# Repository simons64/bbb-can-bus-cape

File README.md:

# bbb-can-bus-cape
beaglebone black cape:
- 4x CANbus (up to 1Mbit, 2x direct CAN, 2x MCP2515)
- 1x RS485 up to 10 Mbit

## __design untested yet !__

Credits for the design to [@voloviq/bbb-can-bus-cape](https://github.com/voloviq/bbb-can-bus-cape)  
Design was adjusted for:
- currently available components from jlcpcb
- compatible interface for home ESS (Victron Multiplus 2 ; Victron MPPT RS 450 ; Pylontech US5000C)

## board 3D view

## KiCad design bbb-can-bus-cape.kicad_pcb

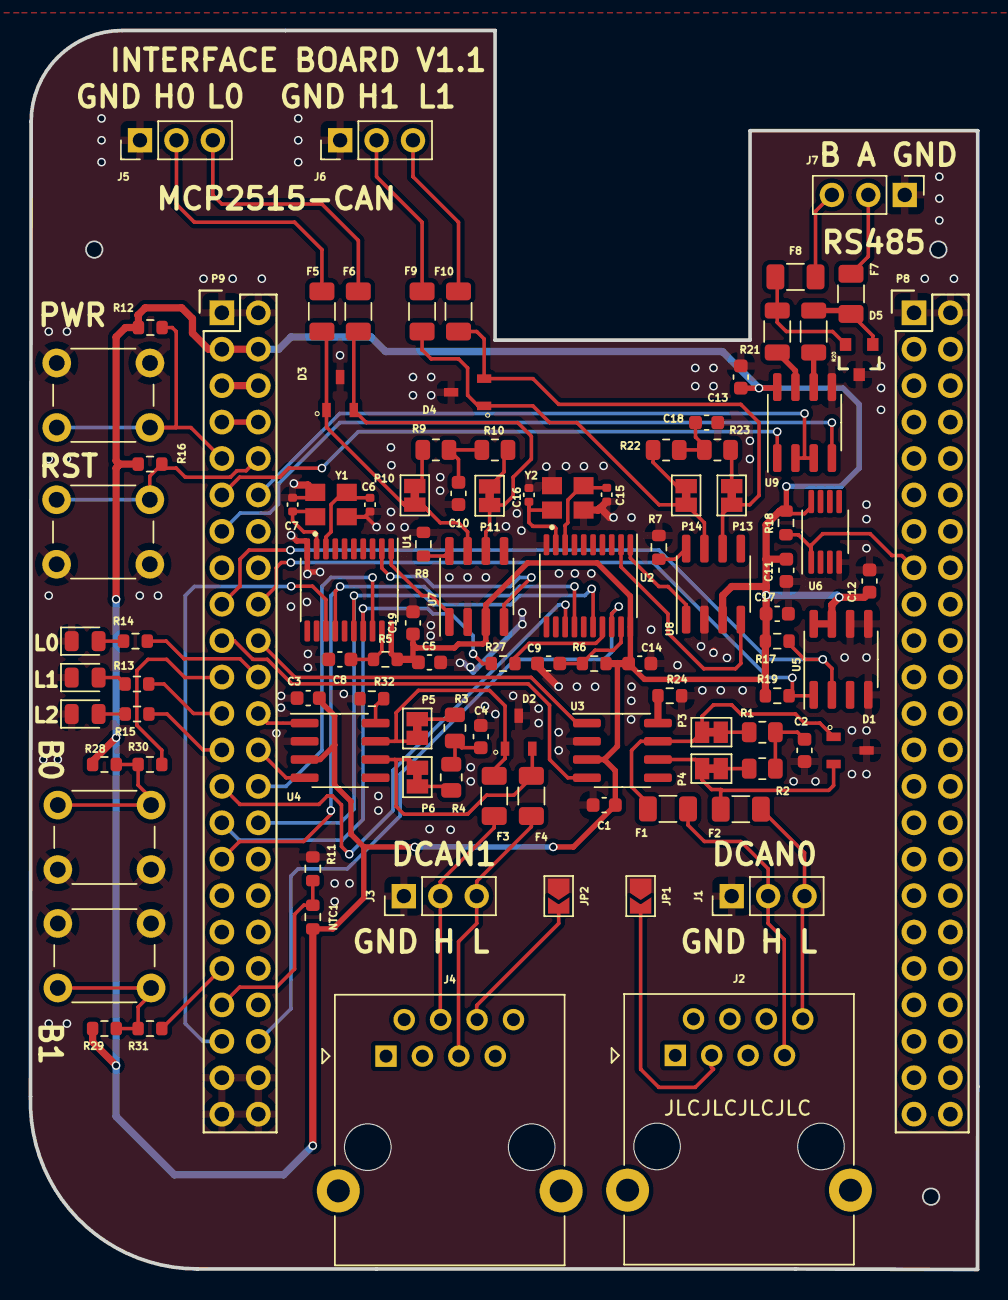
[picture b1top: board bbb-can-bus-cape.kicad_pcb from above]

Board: 2 copper layers, 66.0 x 86.4 mm, 102 parts (0 on the bottom side), 85 nets.

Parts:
C1, C2, C3, C4, C5, C8, C9, C10, C11, C12, C13, C14, C17, C18, C19: 100nF/50V; C_0603_1608Metric
C6, C7, C15, C16: 10pF/50V; C_0402_1005Metric
D1, D2, D3, D4: PESD2CAN,215; SOT95P230X110-3N
D5: PSM712; SOT23-3
D6, D7, D8: LED; D_0805_2012Metric
F1, F2, F3, F4, F5, F6, F7, F8, F9, F10: Polyfuse_Small; Fuse_1206_3216Metric
J1: Conn_DCAN0; PinHeader_1x03_P2.54mm_Vertical
J2: RJ45 BBB-DCAN0; RJ45_Ninigi_GE
J3: Conn_DCAN1; PinHeader_1x03_P2.54mm_Vertical
J4: RJ45 BBB-DCAN1; RJ45_Ninigi_GE
J5: Conn_MCP2515_CAN0; PinHeader_1x03_P2.54mm_Vertical
J6: Conn_MCP2515_CAN1; PinHeader_1x03_P2.54mm_Vertical
J7: Conn_RS485; PinHeader_1x03_P2.54mm_Vertical
JP1, JP2: J2_Open; SolderJumper-2_P1.3mm_Open_TrianglePad1.0x1.5mm
NTC1: NTCS0603E3103FMT; R_0603_1608Metric
P3, P4, P5, P6, P10, P11, P13, P14: TERM; SolderJumper-2_P1.3mm_Bridged_Pad1.0x1.5mm
P8, P9: BeagleBone_Black_Header; Socket_BeagleBone_Black
R1, R2, R3, R4, R9, R10, R22, R23: 60R; R_0805_2012Metric
R5, R6, R7, R8, R24, R32: 10k; R_0603_1608Metric
R11, R12, R16, R17, R18, R19, R28, R29: 4k7; R_0603_1608Metric
R13, R14, R15, R27, R30, R31: 100R; R_0603_1608Metric
R20, R21: 10R; R_1206_3216Metric
Sw1, Sw2, Sw3, Sw4: DTSM-31N; SW_PUSH_6mm
U1, U2: MCP2515-xST; TSSOP-20_4.4x6.5mm_P0.65mm
U3, U4, U7, U8: SN65HVD230; SOIC-8_3.9x4.9mm_P1.27mm
U5: TCN75A; SOIC-8_3.9x4.9mm_P1.27mm
U6: DS18B20U; MSOP-8_3x3mm_P0.65mm
U9: SP3485EN; SOIC-8_3.9x4.9mm_P1.27mm
Y1, Y2: X322516MLB4SI; OSC_X322516MLB4SI

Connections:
3V3: C1.1, C3.1, C5.1, C11.1, C12.1, C13.1, C14.1, C17.1, C19.1, NTC1.2, P9.3, P9.4, R5.2, R6.2, R12.1, R16.1, R17.1, R18.1, R19.1, R28.1, R29.1, U1.20 (VDD), U2.20 (VDD), U3.3 (VCC), U4.3 (VCC), U5.7 (A0), U5.8 (VDD), U6.8 (VDD), U7.3 (VCC), U8.3 (VCC), U9.8 (VCC)
5V: P9.5, P9.6
/AN0: NTC1.1, P9.39, R11.1
/CAN bus0/CAN_H: F1.2, J1.2, J2.7
/CAN bus0/CAN_L: F2.2, J1.3, J2.8
/CAN bus1/CAN_H: F3.2, J3.2, J4.4
/CAN bus1/CAN_L: F4.2, J3.3, J4.5
/DCAN0_RX: P9.19, U3.4 (R)
/DCAN0_TX: P9.20, U3.1 (D)
/DCAN1_RX: P9.24, U4.1 (D)
/DCAN1_TX: P9.26, U4.4 (R)
/GPIO0_2: P9.22, R14.1
/GPIO0_3: P9.21, R30.2
/GPIO0_20: P9.41, U1.13 (~INT)
/GPIO1_17: P9.23, R13.1
/GPIO1_28: P9.12, U9.2 (~RE), U9.3 (DE)
/GPIO3_21: P9.25, R15.1
/I2C1_SCL: P9.17, R17.2, U5.2 (SCL)
/I2C1_SDA: P9.18, R19.2, U5.1 (SDA)
/PWR_BUT: P9.9, R12.2, Sw1.1
/RS485/RS485_A: F7.2, J7.2
/RS485/RS485_B: F8.2, J7.3
/SPI1_CS0: P9.28, U1.18 (~CS)
/SPI1_CS1: P9.42, U2.18 (~CS)
/SPI1_MISO: P9.29, R27.1, U1.17 (SO)
/SPI1_MOSI: P9.30, U1.16 (SI), U2.16 (SI)
/SPI1_SCK: P9.31, U1.14 (SCK), U2.14 (SCK)
/SYS_RESETN: P9.10, R16.2, Sw2.1
/Standalone Can BUS/CAN_H0: F5.2, J5.2
/Standalone Can BUS/CAN_H1: F9.2, J6.2
/Standalone Can BUS/CAN_L0: F6.2, J5.3
/Standalone Can BUS/CAN_L1: F10.2, J6.3
/Standalone Can BUS/CAN_~INT1: P9.27, U2.13 (~INT)
/UART4_RX: P9.11, U9.1 (RO)
/UART4_TX: P9.13, U9.4 (DI)
GND: C1.2, C2.2, C3.2, C4.2, C5.2, C6.2, C7.2, C8.2, C9.2, C10.2, C11.2, C12.2, C13.2, C14.2, C15.2, C16.2, C17.2, C18.2, C19.2, D1.3, D2.3, D3.3, D4.3, D5.3, D6.1 (K), D7.1 (K), D8.1 (K), J1.1, J3.1, J5.1, J6.1, J7.1, JP1.1 (A), JP2.1 (A), P8.1, P8.2, P9.1, P9.2, P9.43, P9.44, P9.45, P9.46, R7.2, R8.2, R11.2, R24.2, R32.2, Sw1.2, Sw2.2, Sw3.2, Sw4.2, U1.10 (VSS), U2.10 (VSS), U3.2 (GND), U4.2 (GND), U5.4 (VSS), U5.5 (A2), U5.6 (A1), U6.4 (VSS), U7.2 (GND), U8.2 (GND), U9.5 (GND), Y1.2, Y1.4, Y2.2, Y2.4
unnamed: C2.1, R1.2, R2.1
unnamed: C4.1, R3.2, R4.1
unnamed: C10.1, R9.2, R10.1
unnamed: C18.1, R22.2, R23.1
unnamed: D5.1, F7.1, R20.2
unnamed: D5.2, F8.1, R21.2
unnamed: D6.2 (A), R13.2
unnamed: D7.2 (A), R14.2
unnamed: D8.2 (A), R15.2
unnamed: J2.3, JP1.2 (B)
unnamed: J4.6, JP2.2 (B)
unnamed: P3.1, R1.1
unnamed: P4.2, R2.2
unnamed: P5.1, R3.1
unnamed: P6.2, R4.2
unnamed: P8.15, R18.2, U6.1 (DQ)
unnamed: P9.37, R31.2
unnamed: P10.1, R9.1
unnamed: P11.2, R10.2
unnamed: P13.1, R22.1
unnamed: P14.2, R23.2
unnamed: R28.2, R30.1, Sw3.1
unnamed: R29.2, R31.1, Sw4.1
unnamed: C7.1, U1.9 (OSC1), Y1.1
unnamed: C6.1, U1.8 (OSC2), Y1.3
unnamed: U1.2 (RXCAN), U7.4 (R)
unnamed: U1.1 (TXCAN), U7.1 (D)
unnamed: C8.1, R5.1, U1.19 (~RESET)
unnamed: C16.1, U2.9 (OSC1), Y2.1
unnamed: C15.1, U2.8 (OSC2), Y2.3
unnamed: U2.2 (RXCAN), U8.4 (R)
unnamed: R27.2, U2.17 (SO)
unnamed: U2.1 (TXCAN), U8.1 (D)
unnamed: C9.1, R6.1, U2.19 (~RESET)
unnamed: D1.1, F1.1, P3.2, U3.7 (CANH)
unnamed: D1.2, F2.1, P4.1, U3.6 (CANL)
unnamed: R24.1, U3.8 (Rs)
unnamed: D2.1, F3.1, P5.2, U4.7 (CANH)
unnamed: D2.2, F4.1, P6.1, U4.6 (CANL)
unnamed: R32.1, U4.8 (Rs)
unnamed: D3.1, F5.1, P10.2, U7.7 (CANH)
unnamed: D3.2, F6.1, P11.1, U7.6 (CANL)
unnamed: R8.1, U7.8 (Rs)
unnamed: D4.1, F9.1, P13.2, U8.7 (CANH)
unnamed: D4.2, F10.1, P14.1, U8.6 (CANL)
unnamed: R7.1, U8.8 (Rs)
unnamed: R20.1, U9.6 (A)
unnamed: R21.1, U9.7 (B)
SYS_5V: P9.7, P9.8

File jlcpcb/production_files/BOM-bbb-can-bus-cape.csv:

Comment,Designator,Footprint,LCSC
SN65HVD230,"U3,U4,U7,U8",SOIC-8_3.9x4.9mm_P1.27mm,C12084
X322516MLB4SI,"Y1,Y2",OSC_X322516MLB4SI,C13738
100nF/50V,"C1,C10,C11,C12,C13,C14,C17,C18,C19,C2,C3,C4,C5,C8,C9",C_0603_1608Metric,C14663
60R,"R1,R10,R2,R22,R23,R3,R4,R9",R_0805_2012Metric,C17757
10R,"R20,R21",R_1206_3216Metric,C17903
100R,"R13,R14,R15,R27,R30,R31",R_0603_1608Metric,C22775
LED,D6,D_0805_2012Metric,C2296
LED,D7,D_0805_2012Metric,C2297
4k7,"R11,R12,R16,R17,R18,R19,R28,R29",R_0603_1608Metric,C23162
10k,"R24,R32,R5,R6,R7,R8",R_0603_1608Metric,C25804
PSM712,D5,SOT23-3,C32677
10pF/50V,"C15,C16,C6,C7",C_0402_1005Metric,C32949
Polyfuse_Small,"F1,F10,F2,F3,F4,F5,F6,F7,F8,F9",Fuse_1206_3216Metric,C438898
"PESD2CAN,215","D1,D2,D3,D4",SOT95P230X110-3N,C75176
LED,D8,D_0805_2012Metric,C84256
SP3485EN,U9,SOIC-8_3.9x4.9mm_P1.27mm,C8963

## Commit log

2023-02-19 created new layout for adjusted schematic
2023-02-19 add new screenshots and change pcb picture
2023-02-19 README.md -> description of design adjustments
2023-09-17 add backups
